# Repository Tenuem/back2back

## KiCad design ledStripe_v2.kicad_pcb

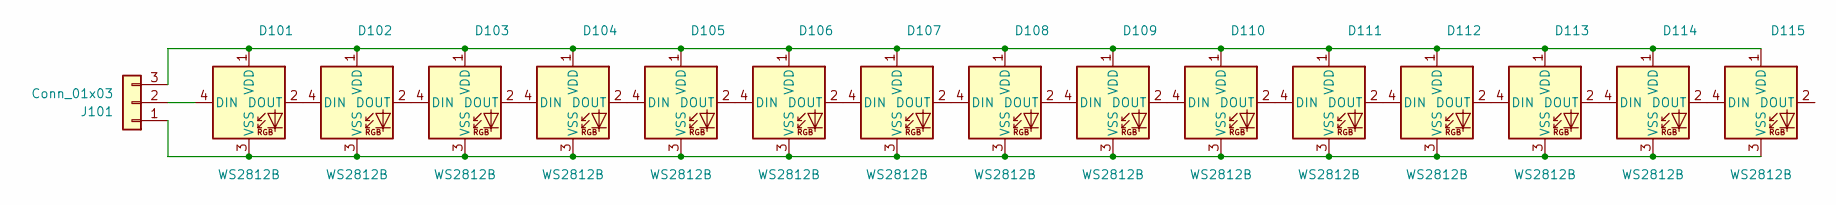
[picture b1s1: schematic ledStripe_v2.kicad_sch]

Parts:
D101, D102, D103, D104, D105, D106, D107, D108, D109, D110, D111, D112, D113, D114, D115: WS2812B; LED_WS2812B_PLCC4_5.0x5.0mm_P3.2mm
J101: Conn_01x03; PinHeader_1x03_P1.27mm_Vertical_SMD_Pin1Right

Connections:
unnamed: D101.1 (VDD), D102.1 (VDD), D103.1 (VDD), D104.1 (VDD), D105.1 (VDD), D106.1 (VDD), D107.1 (VDD), D108.1 (VDD), D109.1 (VDD), D110.1 (VDD), D111.1 (VDD), D112.1 (VDD), D113.1 (VDD), D114.1 (VDD), D115.1 (VDD), J101.3
unnamed: D101.2 (DOUT), D102.4 (DIN)
unnamed: D101.3 (VSS), D102.3 (VSS), D103.3 (VSS), D104.3 (VSS), D105.3 (VSS), D106.3 (VSS), D107.3 (VSS), D108.3 (VSS), D109.3 (VSS), D110.3 (VSS), D111.3 (VSS), D112.3 (VSS), D113.3 (VSS), D114.3 (VSS), D115.3 (VSS), J101.1
unnamed: D101.4 (DIN), J101.2
unnamed: D102.2 (DOUT), D103.4 (DIN)
unnamed: D103.2 (DOUT), D104.4 (DIN)
unnamed: D104.2 (DOUT), D105.4 (DIN)
unnamed: D105.2 (DOUT), D106.4 (DIN)
unnamed: D106.2 (DOUT), D107.4 (DIN)
unnamed: D107.2 (DOUT), D108.4 (DIN)
unnamed: D108.2 (DOUT), D109.4 (DIN)
unnamed: D109.2 (DOUT), D110.4 (DIN)
unnamed: D110.2 (DOUT), D111.4 (DIN)
unnamed: D111.2 (DOUT), D112.4 (DIN)
unnamed: D112.2 (DOUT), D113.4 (DIN)
unnamed: D113.2 (DOUT), D114.4 (DIN)
unnamed: D114.2 (DOUT), D115.4 (DIN)

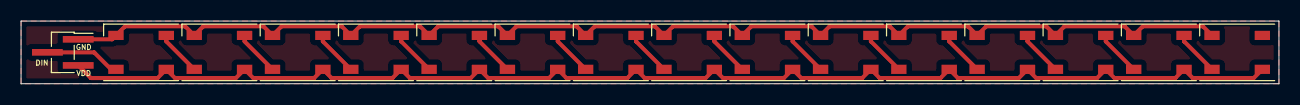
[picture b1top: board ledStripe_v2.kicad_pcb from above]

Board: 2 copper layers, 122.4 x 6.1 mm, 16 parts (0 on the bottom side), 17 nets.

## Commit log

2023-01-19 added basics for pressure sensors
2023-02-09 basic pcb design
2023-02-09 non-default foorprint libs used in my supercomplicated projects
2023-02-09 led stripe with 0.2mm leds
2023-02-09 gitignore added
2023-02-09 brand new narrow ledstripe
2023-02-09 final version
2023-02-09 voltage regulator
2023-02-13 layout and routing

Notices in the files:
ledStripe_v2.kicad_pcb:
Developed by Fantom Factory. ALL RIGHTS RESERVED © 2023
